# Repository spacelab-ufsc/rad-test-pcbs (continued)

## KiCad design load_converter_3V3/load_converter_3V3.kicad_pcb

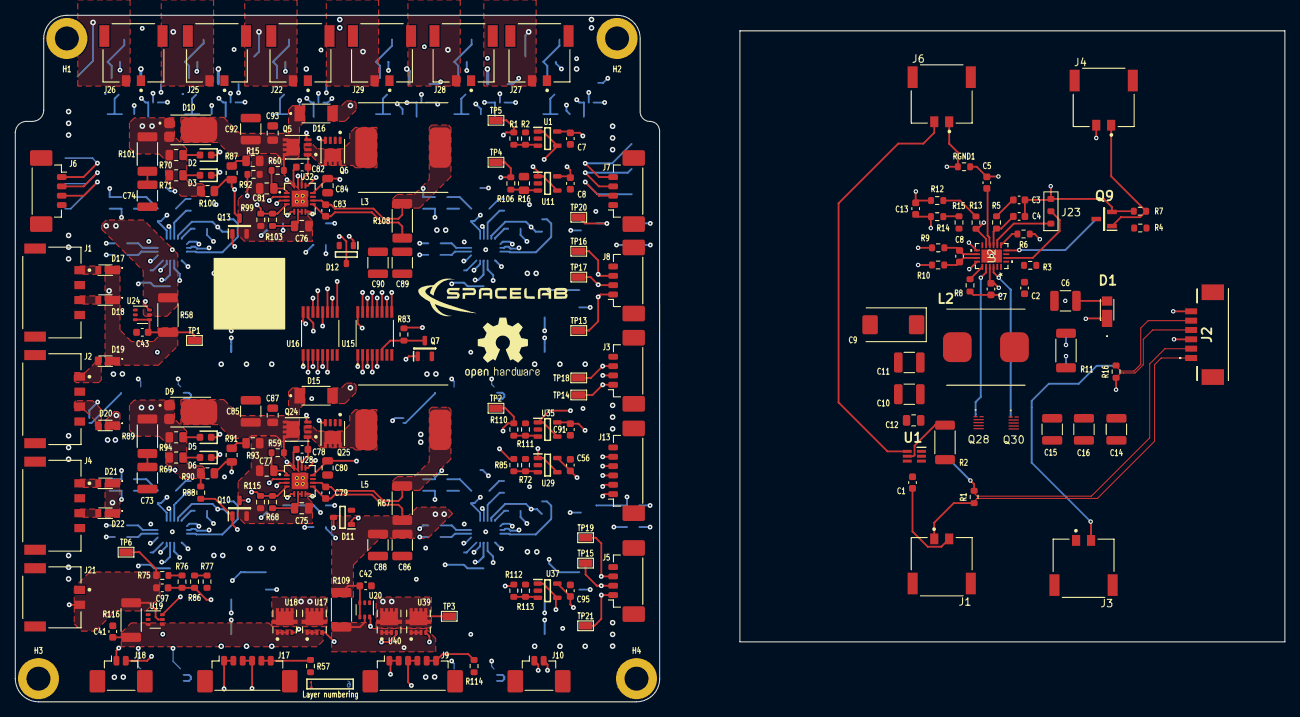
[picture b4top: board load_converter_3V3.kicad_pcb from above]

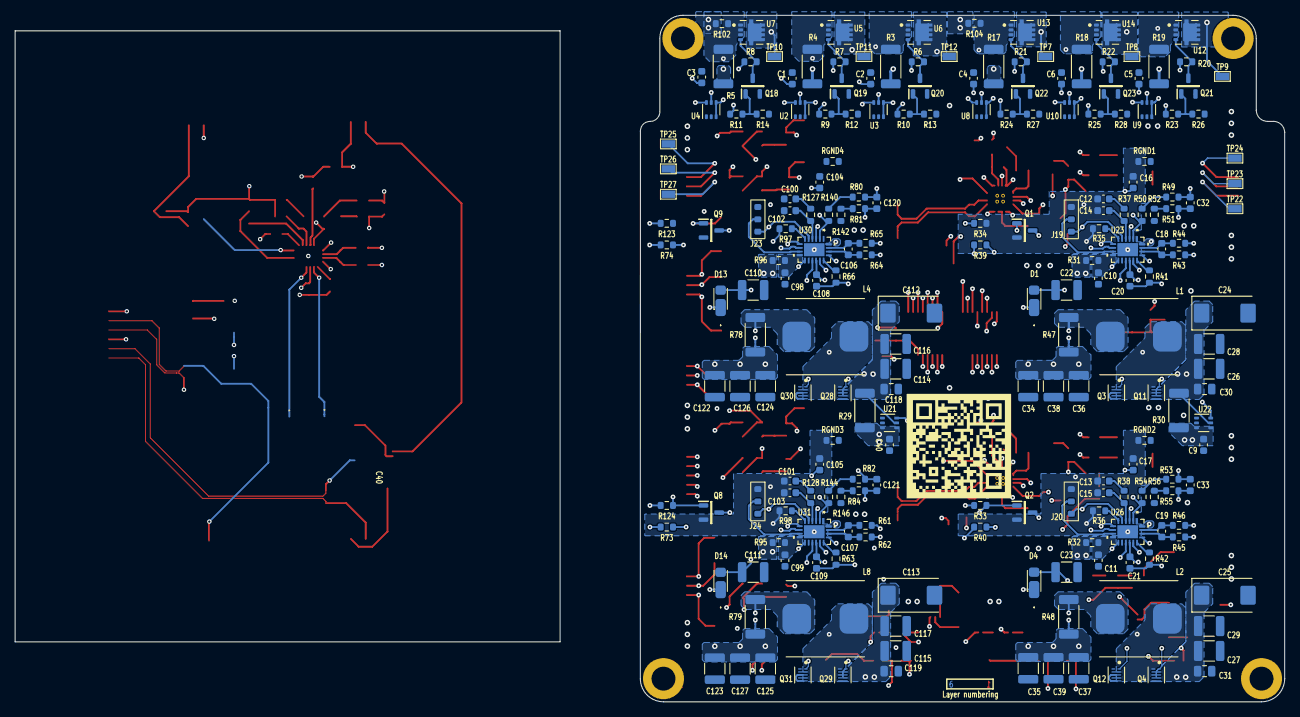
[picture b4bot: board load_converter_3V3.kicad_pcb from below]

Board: 2 copper layers, 86.3 x 91.9 mm, 415 parts (216 on the bottom side), 236 nets.

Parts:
C1, C1#2, C2, C2#2, C3#2, C4#2, C5#2, C6#2, C7, C7#2, C8, C9#2, C10#2, C11#2, C20, C21, C40, C41, C42, C43, C56, C78, C79, C82, C83, C91, C95, C98, C99, C108, C109: 100nF; CAP0603
C3, C12#2, C13#2, C100, C101: 3.3nF; CAP0603
C4, C14#2, C15#2, C102, C103: 100pF; CAP0603
C5, C8#2, C16#2, C17, C18, C19, C104, C105, C106, C107: 1nF; CAP0603
C6, C22, C23, C88, C90, C110, C111: 4.7uF; CAP1210
C9, C24, C25, C112, C113: 47uF; CAP2917POL
C10, C11, C26, C27, C28, C29, C85, C86, C89, C92, C114, C115, C116, C117: 10uF; CAP1210
C12, C30, C31, C75, C76, C77, C80, C81, C84, C87, C93, C118, C119: 1uF; CAP0805
C13, C32, C33, C97, C120, C121: 22pF; CAP0603
C14, C15, C16, C34, C35, C36, C37, C38, C39, C122, C123, C124, C125, C126, C127: 22uF; CAP1210
C73, C74: 2.2uF; CAP1210
D1, D1#2, D4, D13, D14: SS12FP
D2, D3, D5, D6: LTST-C190GKT
D9, D10: PDS1040L-13
D11, D12: BAT54
D15, D16: PMEG3050EP,115
D17, D18, D19, D20, D21, D22: CUHS20S40,H3F
H1, H2, H3, H4: Mounting hole (3.2 mm); MountingHole
J1, J3, J4#2, J6, J21, J22, J25, J26, J27, J28, J29: 2053380002
J1#2, J2#2, J4: 2053380004
J2: 53261-0671; 532610671
J3#2, J5, J6#2, J7, J8: 532610471
J9, J13, J17: 532610671
J10, J18: 532610271
J19, J20, J23, J23#2, J24: N/A; three_position_jumper
JP1, JP2, JP3, JP4, JP5, JP6: N/A; Jumper
L1, L2, L2#2, L4, L8: 2.4uH; 744325240
L3, L5: 12uH; 744770112
Q1, Q2, Q7, Q8, Q9#2, Q10, Q13, Q18, Q19, Q20, Q21, Q22, Q23: SI2302DDS-T1-GE3
Q3, Q4, Q11, Q12, Q28#2, Q29, Q30#2, Q31: EPC2016C
Q5, Q6, Q24, Q25: SI7414DN-T1-E3
Q9: SI2302DDS-T1-GE3; SOT95P237X112-3N
Q28, Q30: EPC2016C; EPC2016C_ECC
R1, R16: 100m; RES0603
R1#2: 13k; RES0603
R2, R29, R30: 5m; RES2010
R2#2, R15, R52, R56, R142, R146: 20k; RES0603
R3, R31, R32, R95, R96: 2.2R; RES0603
R3#2, R4#2, R67, R108: 33m; RES2010
R4, R7, R12#2, R13#2, R14#2, R26, R27, R28, R33, R34, R39, R40, R57, R73, R74, R83, R88, R92, R114, R123, R124: 100k; RES0603
R5, R37, R38, R127, R128: 12k; RES0603
R5#2: 18m; RES2010
R6, R35, R36, R97, R98: 82k; RES0603
R6#2, R7#2, R8#2, R85: 30k; RES0603
R8, R9, R10, R41, R42, R43, R44, R45, R46, R59, R60, R61, R62, R63, R64, R65, R66: 10R; RES0603
R9#2, R10#2, R11#2, R23, R24, R25: 470R; RES0603
R11, R18, R19, R47, R48, R78, R79: 16m; RES2010
R12, R14, R49, R51, R53, R55, R76, R77, R80, R81, R82, R84, R102, R104: 0R; RES0603
R13, R140, R144: 90.9k; RES0603
R15#2, R87, R91, R93: 20k; RES0805
R16#2, R69, R70, R71, R94: 10k; RES0805
R17, R109: 20m; RES2010
R20, R21, R22: 47k; RES0603
R50, R54: 150k; RES0603
R58: 25m; RES2010
R68, R103: 5.23k; RES0603
R72: 8.2k; RES0603
R75: 110k; RES0603
R86: 37.4k; RES0603
R89, R101: 2R; RES2010
R90, R100: 270k; RES0805
R99, R115: 30.1k; RES0603
R106: 15k; RES0603
R110, R112: 24k; RES0603
R111, R113: 7.5k; RES0603
R116: 8m; RES2010
RGND1, RGND1#2, RGND2, RGND3, RGND4: 0R; RES0603
TP1, TP2, TP3, TP4, TP5, TP6, TP7, TP8, TP9, TP10, TP11, TP12, TP13, TP14, TP15, TP16, TP17, TP18, TP19, TP20, TP21, TP22, TP23, TP24, TP25, TP26, TP27: Test point; testpoint_smd
U1: INA199C3DCKR; SOT65P210X110-6N
U1#2, U11, U29, U35, U37: LMV321RIYLT
U2: LTC3833EUDC#TRPBF; QFN-20_UDC_LIT
U2#2, U3, U9, U10, U19, U21, U22: INA199C3DCKR
U4, U8, U20, U24: INA199C1DCKR
U5, U6, U7, U12, U13, U14, U17, U18, U39, U40: NVTFS5116PLTAG
U15, U16: CD4051BPWR
U23, U26, U30, U31: LTC3833EUDC#TRPBF
U28, U32: BQ24650RVAT

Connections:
+3V3: C1#2.2, C2#2.2, C3#2.2, C7.2, C8.2, C56.2, C91.2, C95.2, C120.2, C121.2, C122.2, C123.2, C124.2, C125.2, C126.2, C127.2, JP3.2 (B), JP4.2 (B), R1#2.2, R3#2.1, R4#2.1, R5#2.1, R78.2, R79.2, R80.1, R82.1, R83.2, TP5.1, U1#2.5 (V+), U2#2.3 (V+), U2#2.4 (IN+), U3.3 (V+), U3.4 (IN+), U4.3 (V+), U4.4 (IN+), U11.5 (V+), U15.16 (VCC), U16.16 (VCC), U29.5 (V+), U30.8 (EXTVCC), U30.20 (VOUT), U31.8 (EXTVCC), U31.20 (VOUT), U35.5 (V+), U37.5 (V+)
+5V: C4#2.2, C5#2.2, C6#2.2, C32.2, C33.2, C34.2, C35.2, C36.2, C37.2, C38.2, C39.2, JP1.2 (B), JP2.2 (B), R17.1, R18.1, R19.1, R47.2, R48.2, R49.1, R53.1, R106.2, TP4.1, U8.3 (V+), U8.4 (IN+), U9.3 (V+), U9.4 (IN+), U10.3 (V+), U10.4 (IN+), U23.8 (EXTVCC), U23.20 (VOUT), U26.8 (EXTVCC), U26.20 (VOUT)
/3V3: C13.2, C14.2, C15.2, C16.2, J2.4, R10.1, R11.2, R12.1, R16.1, U2.8 (EXTVCC), U2.20 (VOUT)
/3V3_A_~EN: J3#2.2, Q9#2.1 (G), R123.2, TP20.1
/3V3_AntDep: J27.2, R102.2, TP10.1, U7.5-6-7-8
/3V3_B_~EN: J5.1, Q8.1 (G), R124.1, TP21.1
/3V3_Beacon: J28.2, TP11.1, U5.5-6-7-8
/3V3_OBDH: J29.2, TP12.1, U6.5-6-7-8
/3V3_SENSE1+: L2.2, R9.1, R11.1
/3V3_VCC1: C6.1, D1.2 (A), J23.1, R4.2, U2.5 (VRNG), U2.11 (INTVCC)
/5V0_A_~EN: J3#2.3, Q1.1 (G), R34.2, TP18.1
/5V0_B_~EN: J5.3, Q2.1 (G), R33.1, TP19.1
/5V0_Payload: J22.2, R104.2, TP7.1, U13.5-6-7-8
/5V0_RadioBeacon: J25.2, TP8.1, U14.5-6-7-8
/5V0_RadioMain: J26.2, TP9.1, U12.5-6-7-8
/AMUX0: U16.14 (Y1), U24.6 (OUT)
/AMUX1: U16.15 (Y2), U29.1, U29.4 (-)
/AMUX2: U16.2 (Y6), U20.6 (OUT)
/AMUX3: U16.12 (Y3), U35.1, U35.4 (-)
/AMUX4: U16.1 (Y4), U19.6 (OUT)
/AMUX5: U16.4 (Y7), U37.1, U37.4 (-)
/AMUX6: U16.13 (Y0), U22.6 (OUT)
/AMUX7: U16.5 (Y5), U21.6 (OUT)
/AMUX8: U8.6 (OUT), U15.14 (Y1)
/AMUX9: U9.6 (OUT), U15.1 (Y4)
/AMUX10: U10.6 (OUT), U15.15 (Y2)
/AMUX11: U11.1, U11.4 (-), U15.5 (Y5)
/AMUX12: U4.6 (OUT), U15.2 (Y6)
/AMUX13: U2#2.6 (OUT), U15.12 (Y3)
/AMUX14: U3.6 (OUT), U15.13 (Y0)
/AMUX15: U1#2.1, U1#2.4 (-), U15.4 (Y7)
/AMUX_OUT: J13.5, U15.3 (Z), U16.3 (Z)
/AMUX_SEL0: J13.2, U15.11 (S0), U16.11 (S0)
/AMUX_SEL1: J13.3, U15.10 (S1), U16.10 (S1)
/AMUX_SEL2: J13.4, U15.9 (S2), U16.9 (S2)
/AMUX_SEL3: J13.1, Q7.1 (G), U16.6 (~E)
/AntDep_EN: J7.4, R11#2.2, TP25.1
/BC_A_TS: J8.3, R99.2, R103.1, TP16.1, U32.4 (TS)
/BC_A_~EN: J3#2.1, Q13.1 (G), R92.2, TP14.1
/BC_B_TS: J8.2, R68.1, R115.2, TP17.1, U28.4 (TS)
/BC_B_~EN: J5.2, Q10.1 (G), R88.1, TP15.1
/BC_VFB: C97.1, J8.1, R76.2, R86.2, TP13.1, U28.8 (VFB), U32.8 (VFB)
/Beacon_EN: J7.3, R9#2.2, TP26.1
/OBDH_EN: J7.2, R10#2.2, TP27.1
/Payload_EN: J6#2.3, R24.2, TP22.1
/RadioBeacon_EN: J6#2.2, R25.2, TP23.1
/RadioMain_EN: J6#2.1, R23.2, TP24.1
/U_3V3_Load_Converters/3V3_SENSE1+: L4.2, R64.1, R78.1
/U_3V3_Load_Converters/3V3_SENSE1-: JP4.1 (A), R65.1
/U_3V3_Load_Converters/3V3_SENSE2+: L8.2, R62.1, R79.1
/U_3V3_Load_Converters/3V3_SENSE2-: JP3.1 (A), R61.1
/U_3V3_Load_Converters/3V3_VCC1: C110.1, D13.2 (A), J23#2.1, R74.2, U30.5 (VRNG), U30.11 (INTVCC)
/U_3V3_Load_Converters/3V3_VCC2: C111.1, D14.2 (A), J24.1, R73.2, U31.5 (VRNG), U31.11 (INTVCC)
/U_3V3_Load_Converters/VBUS_BK3V3: C112.1, C113.1, C114.2, C115.2, C116.2, C117.2, C118.2, C119.2, Q28#2.3 (Drain), Q28#2.5 (Drain), Q29.3 (Drain), Q29.5 (Drain), R29.2, R95.2, R96.2, R124.2, U21.5 (IN-)
/U_5V0_Load_Converters/5V0_SENSE1+: L1.2, R43.1, R47.1
/U_5V0_Load_Converters/5V0_SENSE1-: JP2.1 (A), R44.1
/U_5V0_Load_Converters/5V0_SENSE2+: L2#2.2, R45.1, R48.1
/U_5V0_Load_Converters/5V0_SENSE2-: JP1.1 (A), R46.1
/U_5V0_Load_Converters/5V0_VCC1: C22.1, D1#2.2 (A), J19.1, R39.2, U23.5 (VRNG), U23.11 (INTVCC)
/U_5V0_Load_Converters/5V0_VCC2: C23.1, D4.2 (A), J20.1, R40.2, U26.5 (VRNG), U26.11 (INTVCC)
/U_5V0_Load_Converters/VBUS_BK5V0: C24.1, C25.1, C26.2, C27.2, C28.2, C29.2, C30.2, C31.2, Q4.3 (Drain), Q4.5 (Drain), Q11.3 (Drain), Q11.5 (Drain), R30.2, R31.2, R32.2, R33.2, U22.5 (IN-)
/U_Energy Distribution/VBAT: C97.2, J9.1, J9.2, J10.2, J17.1, J17.2, J18.2, J21.2, R75.2, R116.1, TP6.1, U19.5 (IN-)
/U_MPPT_Batery_Charger/BTST1: C82.2, D12.3, U32.16 (BTST)
/U_MPPT_Batery_Charger/BTST2: C78.2, D11.3, U28.16 (BTST)
/U_MPPT_Batery_Charger/MPPT_SENSE1+: C83.2, L3.2, R108.2, U32.10 (SRP)
/U_MPPT_Batery_Charger/MPPT_SENSE1-: C83.1, JP5.1 (A), U32.9 (SRN)
/U_MPPT_Batery_Charger/MPPT_SENSE2+: C79.2, L5.2, R67.2, U28.10 (SRP)
/U_MPPT_Batery_Charger/MPPT_SENSE2-: C79.1, JP6.1 (A), U28.9 (SRN)
/U_MPPT_Batery_Charger/PH1: C82.1, L3.1, Q5.1 (S), Q5.2 (S), Q5.3 (S), Q6.5-6-7-8 (D), U32.14 (PH)
/U_MPPT_Batery_Charger/PH2: C78.1, L5.1, Q24.1 (S), Q24.2 (S), Q24.3 (S), Q25.5-6-7-8 (D), U28.14 (PH)
/U_MPPT_Batery_Charger/REGN1: C84.2, D12.1, U32.12 (REGN)
/U_MPPT_Batery_Charger/REGN2: C80.2, D11.1, U28.12 (REGN)
/U_MPPT_Batery_Charger/VBC_IN: D9.1, D9.2, D10.1, D10.2, R58.2, R69.1, R70.1, R71.1, R85.2, R88.2, R89.2, R90.2, R94.1, R100.2, R101.2, U24.5 (IN-)
/U_MPPT_Batery_Charger/VBC_OUT: C42.2, C86.2, C88.2, C89.2, C90.2, D15.2 (A), D16.2 (A), JP5.2 (B), JP6.2 (B), R67.1, R108.1, R109.1, U20.3 (V+), U20.4 (IN+)
/U_MPPT_Batery_Charger/VCC1: C81.2, R60.1, U32.1 (VCC)
/U_MPPT_Batery_Charger/VCC2: C77.2, R59.1, U28.1 (VCC)
/U_MPPT_Batery_Charger/VREF1: C76.2, R103.2, U32.6 (VREF), U32.7 (TERM_EN)
/U_MPPT_Batery_Charger/VREF2: C75.2, R68.2, U28.6 (VREF), U28.7 (TERM_EN)
/VBUS_BK3V3: C9.1, C10.2, C11.2, C12.2, Q28.3 (Drain), Q28.5 (Drain), R2.2, R3.2, U1.5 (IN-)
/VIN: R109.2, R110.1, TP2.1, U20.5 (IN-), U39.1, U39.2, U39.3, U40.1, U40.2, U40.3
/VPANELS: C43.2, D17.1, D18.1, D19.1, D20.1, D21.1, D22.1, R58.1, TP1.1, U24.3 (V+), U24.4 (IN+)
/X+Panels: D17.2, J1#2.1
/X-Panels: D18.2, J1#2.3
/Y+Panels: D19.2, J2#2.1
/Y-Panels: D20.2, J2#2.3
/Z+Panels: D21.2, J4.1
/Z-Panels: D22.2, J4.3
GNDPWR: C1.1, C1#2.1, C2.2, C2#2.1, C3#2.1, C4#2.1, C5#2.1, C6.2, C6#2.1, C7.1, C8.1, C9.2, C9#2.1, C10.1, C10#2.2, C11.1, C11#2.2, C12.1, C14.1, C15.1, C16.1, C22.2, C23.2, C24.2, C25.2, C26.1, C27.1, C28.1, C29.1, C30.1, C31.1, C34.1, C35.1, C36.1, C37.1, C38.1, C39.1, C40.1, C41.1, C42.1, C43.1, C56.1, C73.1, C74.1, C80.1, C84.1, C85.1, C86.1, C87.1, C88.1, C89.1, C90.1, C91.1, C92.1, C93.1, C95.1, C98.2, C99.2, C110.2, C111.2, C112.2, C113.2, C114.1, C115.1, C116.1, C117.1, C118.1, C119.1, C122.1, C123.1, C124.1, C125.1, C126.1, C127.1, J1.2, J1#2.2, J1#2.4, J2.6, J2#2.2, J2#2.4, J3.1, J3#2.4, J4.2, J4.4, J4#2.2, J5.4, J6.1, J6#2.4, J7.1, J8.4, J13.6, J21.1, J22.1, J25.1, J26.1, J27.1, J28.1, J29.1, Q3.2 (Substrate), Q3.4 (Source), Q3.6 (Source), Q6.1 (S), Q6.2 (S), Q6.3 (S), Q7.2 (S), Q12.2 (Substrate), Q12.4 (Source), Q12.6 (Source), Q18.2 (S), Q19.2 (S), Q20.2 (S), Q21.2 (S), Q22.2 (S), Q23.2 (S), Q25.1 (S), Q25.2 (S), Q25.3 (S), Q30.2 (Substrate), Q30.4 (Source), Q30.6 (Source), Q30#2.2 (Substrate), Q30#2.4 (Source), Q30#2.6 (Source), Q31.2 (Substrate), Q31.4 (Source), Q31.6 (Source), R2#2.2, R12#2.1, R13#2.1, R14#2.1, R15.1, R16#2.2, R26.1, R27.1, R28.1, R52.1, R56.1, R57.2, R72.1, R77.2, R111.2, R113.1, R114.1, R142.1, R146.1, RGND1.2, RGND1#2.2, RGND2.2, RGND3.2, RGND4.2, U1.1 (REF), U1.2 (GND), U1#2.2 (V-), U2.1 (VOSNS-), U2.12 (PGND), U2#2.1 (REF), U2#2.2 (GND), U3.1 (REF), U3.2 (GND), U4.1 (REF), U4.2 (GND), U8.1 (REF), U8.2 (GND), U9.1 (REF), U9.2 (GND), U10.1 (REF), U10.2 (GND), U11.2 (V-), U15.7 (VEE), U15.8 (GND), U16.7 (VEE), U16.8 (GND), U19.1 (REF), U19.2 (GND), U20.1 (REF), U20.2 (GND), U21.1 (REF), U21.2 (GND), U22.1 (REF), U22.2 (GND), U23.1 (VOSNS-), U23.12 (PGND), U24.1 (REF), U24.2 (GND), U26.1 (VOSNS-), U26.12 (PGND), U28.11 (GND), U28.18 (THERMAL_VIA), U29.2 (V-), U30.1 (VOSNS-), U30.12 (PGND), U31.1 (VOSNS-), U31.12 (PGND), U32.11 (GND), U32.18 (THERMAL_VIA), U35.2 (V-), U37.2 (V-)
GNDS1: C12#2.1, C14#2.1, C16#2.1, J19.3, Q1.2 (S), R34.1, R35.1, RGND1#2.1, U23.21 (EPAD)
GNDS2: C13#2.1, C15#2.1, C17.1, J20.3, Q2.2 (S), R36.1, RGND2.1, U26.21 (EPAD)
GNDS3: C3.1, C4.1, C5.1, C100.1, C102.1, C104.1, J23.3, J23#2.3, Q9.2 (S), Q9#2.2 (S), R6.1, R7.1, R97.1, R123.1, RGND1.1, RGND4.1, U2.21 (EPAD), U30.21 (EPAD)
GNDS4: C101.1, C103.1, C105.1, J24.3, Q8.2 (S), R98.1, RGND3.1, U31.21 (EPAD)
GNDS5: C76.1, C81.1, Q13.2 (S), R15#2.1, R92.1, R99.1, U32.17 (EPAD)
GNDS6: C75.1, C77.1, Q10.2 (S), R93.1, R115.1, U28.17 (EPAD)
unnamed: C3.2, R5.2
unnamed: C12#2.2, R37.1
unnamed: C13#2.2, R38.1
unnamed: C73.2, R89.1
unnamed: C74.2, R101.1
unnamed: C100.2, R127.2
unnamed: C101.2, R128.1
unnamed: C7#2.2, C20.2, D1.1 (K), D1#2.1 (K), R8.1, R41.1
unnamed: D2.2, R70.2
unnamed: D3.2, R71.2
unnamed: C21.2, D4.1 (K), R42.1
unnamed: D5.2, R94.2
unnamed: D6.2, R69.2
unnamed: C108.2, D13.1 (K), R66.1
unnamed: C109.2, D14.1 (K), R63.1
unnamed: C85.2, C87.2, D9.3, D15.1 (K), Q24.5-6-7-8 (D), R59.2
unnamed: C92.2, C93.2, D10.3, D16.1 (K), Q5.5-6-7-8 (D), R60.2
unnamed: J1.1, J2.1, R1.1
unnamed: J2.5, J3.2, R16.2
unnamed: J9.5, J9.6, R114.2
unnamed: J9.3, J9.4, J10.1, U39.4, U40.4
unnamed: J17.3, J17.4, J18.1, U17.4, U18.4
unnamed: J17.5, J17.6, R57.1
unnamed: Q1.3 (D), U23.7 (RUN)
unnamed: Q2.3 (D), U26.7 (RUN)
unnamed: Q3.1 (Gate), U23.13 (BG)
unnamed: Q4.1 (Gate), U26.15 (TG)
unnamed: C21.1, L2#2.1, Q4.2 (Substrate), Q4.4 (Source), Q4.6 (Source), Q12.3 (Drain), Q12.5 (Drain), U26.14 (SW)
unnamed: Q5.4 (G), U32.15 (HIDRV)
unnamed: Q6.4 (G), U32.13 (LODRV)
unnamed: Q7.3 (D), R83.1, U15.6 (~E)
unnamed: Q8.3 (D), U31.7 (RUN)
unnamed: Q9.3 (D), Q9#2.3 (D), U2.7 (RUN), U30.7 (RUN)
unnamed: J4#2.1, Q9.1 (G), R7.2
unnamed: Q10.3 (D), R90.1, R91.2, U28.2 (MPPSET)
unnamed: Q11.1 (Gate), U23.15 (TG)
unnamed: C20.1, L1.1, Q3.3 (Drain), Q3.5 (Drain), Q11.2 (Substrate), Q11.4 (Source), Q11.6 (Source), U23.14 (SW)
unnamed: Q12.1 (Gate), U26.13 (BG)
unnamed: Q13.3 (D), R87.2, R100.1, U32.2 (MPPSET)
unnamed: Q18.3 (D), R8#2.1, U7.4
unnamed: Q18.1 (G), R11#2.1, R14#2.2
unnamed: Q19.3 (D), R7#2.1, U5.4
unnamed: Q19.1 (G), R9#2.1, R12#2.2
unnamed: Q20.3 (D), R6#2.1, U6.4
unnamed: Q20.1 (G), R10#2.1, R13#2.2
unnamed: Q21.3 (D), R20.1, U12.4
unnamed: Q21.1 (G), R23.1, R26.2
unnamed: Q22.3 (D), R21.1, U13.4
unnamed: Q22.1 (G), R24.1, R27.2
unnamed: Q23.3 (D), R22.1, U14.4
unnamed: Q23.1 (G), R25.1, R28.2
unnamed: Q24.4 (G), U28.15 (HIDRV)
unnamed: Q25.4 (G), U28.13 (LODRV)
unnamed: Q28.1 (Gate), Q28#2.1 (Gate), U2.15 (TG), U30.15 (TG)
unnamed: C7#2.1, C108.1, L2.1, L4.1, Q28.2 (Substrate), Q28.4 (Source), Q28.6 (Source), Q28#2.2 (Substrate), Q28#2.4 (Source), Q28#2.6 (Source), Q30.3 (Drain), Q30.5 (Drain), Q30#2.3 (Drain), Q30#2.5 (Drain), U2.14 (SW), U30.14 (SW)
unnamed: Q29.1 (Gate), U31.15 (TG)
unnamed: C109.1, L8.1, Q29.2 (Substrate), Q29.4 (Source), Q29.6 (Source), Q31.3 (Drain), Q31.5 (Drain), U31.14 (SW)
unnamed: Q30.1 (Gate), Q30#2.1 (Gate), U2.13 (BG), U30.13 (BG)
unnamed: Q31.1 (Gate), U31.13 (BG)
unnamed: R12.2, R13.2
unnamed: R14.2, R15.2
unnamed: R15#2.2, R87.1
unnamed: R49.2, R50.2
unnamed: R51.2, R52.2
unnamed: R53.2, R54.2
unnamed: R55.2, R56.2
unnamed: R75.1, R76.1
unnamed: R77.1, R86.1
unnamed: R91.1, R93.2
unnamed: R80.2, R140.2
unnamed: R81.2, R142.2
unnamed: R82.2, R144.2
unnamed: R84.2, R146.2
unnamed: R1#2.1, R2#2.1, U1#2.3 (+)
unnamed: C1.2, J2.2, R1.2, R2.1, U1.3 (V+), U1.4 (IN+)
unnamed: J6.2, U1.6 (OUT)
unnamed: R8.2, U2.16 (BOOST)
unnamed: R4#2.2, R7#2.2, U2#2.5 (IN-), U5.1, U5.2, U5.3
unnamed: C4.2, R5.1, U2.4 (ITH)
unnamed: J23.2, U2.9 (MODE/PLLIN)
unnamed: J2.3, R4.1, U2.17 (PGOOD)
unnamed: R6.2, U2.6 (RT)
unnamed: C8#2.2, R9.2, U2.18 (SENSE+)
unnamed: C8#2.1, R10.2, U2.19 (SENSE-)
unnamed: C5.2, U2.3 (TRACK/SS)
unnamed: C2.1, R3.1, U2.10 (VIN)
unnamed: C13.1, R13.1, R14.1, U2.2 (VOSNS+)
unnamed: R3#2.2, R6#2.2, U3.5 (IN-), U6.1, U6.2, U6.3
unnamed: R5#2.2, R8#2.2, R102.1, U4.5 (IN-), U7.1, U7.2, U7.3
unnamed: R17.2, R21.2, R104.1, U8.5 (IN-), U13.1, U13.2, U13.3
unnamed: R19.2, R20.2, U9.5 (IN-), U12.1, U12.2, U12.3
unnamed: R18.2, R22.2, U10.5 (IN-), U14.1, U14.2, U14.3
unnamed: R16#2.1, R106.1, U11.3 (+)
unnamed: C41.2, R116.2, U17.1, U17.2, U17.3, U18.1, U18.2, U18.3, U19.3 (V+), U19.4 (IN+)
unnamed: R41.2, U23.16 (BOOST)
unnamed: C14#2.2, R37.2, U23.4 (ITH)
unnamed: J19.2, U23.9 (MODE/PLLIN)
unnamed: R39.1, U23.17 (PGOOD)
unnamed: R35.2, U23.6 (RT)
unnamed: C18.2, R43.2, U23.18 (SENSE+)
unnamed: C18.1, R44.2, U23.19 (SENSE-)
unnamed: C16#2.2, U23.3 (TRACK/SS)
unnamed: C10#2.1, R31.1, U23.10 (VIN)
unnamed: C32.1, R50.1, R51.1, U23.2 (VOSNS+)
unnamed: R42.2, U26.16 (BOOST)
unnamed: C15#2.2, R38.2, U26.4 (ITH)
unnamed: J20.2, U26.9 (MODE/PLLIN)
unnamed: R40.1, U26.17 (PGOOD)
unnamed: R36.2, U26.6 (RT)
unnamed: C19.2, R45.2, U26.18 (SENSE+)
unnamed: C19.1, R46.2, U26.19 (SENSE-)
unnamed: C17.2, U26.3 (TRACK/SS)
unnamed: C11#2.1, R32.1, U26.10 (VIN)
unnamed: C33.1, R54.1, R55.1, U26.2 (VOSNS+)
unnamed: D5.1, U28.3 (STAT1)
unnamed: D6.1, U28.5 (STAT2)
unnamed: R72.2, R85.1, U29.3 (+)
unnamed: R66.2, U30.16 (BOOST)
unnamed: C102.2, R127.1, U30.4 (ITH)
unnamed: J23#2.2, U30.9 (MODE/PLLIN)
unnamed: R74.1, U30.17 (PGOOD)
unnamed: R97.2, U30.6 (RT)
unnamed: C106.2, R64.2, U30.18 (SENSE+)
unnamed: C106.1, R65.2, U30.19 (SENSE-)
unnamed: C104.2, U30.3 (TRACK/SS)
unnamed: C98.1, R96.1, U30.10 (VIN)
unnamed: C120.1, R81.1, R140.1, U30.2 (VOSNS+)
unnamed: R63.2, U31.16 (BOOST)
unnamed: C103.2, R128.2, U31.4 (ITH)
unnamed: J24.2, U31.9 (MODE/PLLIN)
unnamed: R73.1, U31.17 (PGOOD)
unnamed: R98.2, U31.6 (RT)
unnamed: C107.2, R62.2, U31.18 (SENSE+)
unnamed: C107.1, R61.2, U31.19 (SENSE-)
unnamed: C105.2, U31.3 (TRACK/SS)
unnamed: C99.1, R95.1, U31.10 (VIN)
unnamed: C121.1, R84.1, R144.1, U31.2 (VOSNS+)
unnamed: D2.1, U32.3 (STAT1)
unnamed: D3.1, U32.5 (STAT2)
unnamed: R110.2, R111.1, U35.3 (+)
unnamed: R112.1, R113.2, U37.3 (+)
VBUS: C9#2.2, C40.2, R29.1, R30.1, R112.2, TP3.1, U17.5-6-7-8, U18.5-6-7-8, U21.3 (V+), U21.4 (IN+), U22.3 (V+), U22.4 (IN+), U39.5-6-7-8, U40.5-6-7-8

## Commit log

2025-08-17 chore: add the README.md file from RE²PS project with small changes
2025-08-23 3V3 buck converters project (unfinished)
2025-08-23 project finished
2025-08-23 needs to be revised
2025-09-16 needs review
